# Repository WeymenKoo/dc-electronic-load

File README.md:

# DC Electronic Load

A 150 W programmable DC load (0.6 to 58 V, 0 to 10.1 A) for testing power supplies, batteries and precision current sources.
Built to be better than the AliExpress DL24-class loads and far cheaper than a bench load: four TO-247 MOSFETs each with its own
current loop, hardware CC and CV, real protection, 16-bit readback, galvanic isolation from the PC, and a local OLED + encoder panel so
no computer is needed for simple tests. One USB-C port powers it and carries SCPI (CDC) and DFU.

**Current revision: Rev E** (schematic complete and verified; 2-layer PCB panel created with every part placed, routing not started).
Rev E is the Rev D architecture built as cheaply as JLCPCB / LCSC allow: about US$25 of catalogue parts per unit plus the OLED module,
blower and PCB (`docs/rev_e_specification.md`, section 14). Rev D (Nov 2026) was the same architecture with LT1014 / LT1013 op-amps, a
MAX7219 7-segment panel, a 12 V boost for the fan and a 4-layer panel; Rev B was built in Nov 2024 as two Altium boards; Rev C was a
redesign of the power board around the Rev B control board.

## Folder map

| Folder | What is in it |
|---|---|
| `hardware/` | **Rev E KiCad 10 project**, project libraries, the generator, netlist checker, placer and JLCPCB pricing tools, outputs (PDF schematic, ERC, BOM with LCSC codes and prices, placed-board drawing). See `hardware/README.md` |
| `simulation/` | LTspice decks 00 to 06 for the Rev C analog stage (LT1014 / LT1013, reference results kept) and `rev_e/` with decks 01 to 04 and 06 re-run on the TLV9154. README with both results tables |
| `docs/` | `rev_e_specification.md` (ratings, architecture, isolation, thresholds, layout rules, bring-up, open items, cost), `firmware_requirements.md`, `design_review_rev_b.md` (why Rev B was replaced), MOSFET selection, heatsink plan, comparison with the cheap loads, Rev B design notes spreadsheet |
| `datasheets/` | component datasheets and app notes (`appnotes/`) |
| `reference/` | other people's DC load designs used as references (Scullcom, Jay Diddy B, Kerry Wong) and heatsink / cooler CAD |
| `archive/` | the built Altium revisions: Rev A (May 2024), Rev A2 "cheaper" (Jul 2024), Rev B control, power and UI boards (Nov 2024) with gerbers, the Rev B bring-up firmware, the Rev B netlists used for the review, early LTspice experiments |

## Start here
1. `docs/rev_e_specification.md`: what the instrument is, what Rev E changed to get the cost down, and why every block exists.
2. `hardware/outputs/rev_e_v1/DC_Load_RevE_schematic.pdf`: 14 pages, page 1 is the block diagram. `BOM_RevE_JLC.csv` is the priced BOM.
3. `simulation/README.md`, then open `simulation/rev_e/01_dc_transfer/01_dc_transfer.asc` in LTspice.
4. `docs/design_review_rev_b.md` if you want to know what went wrong before.

## Status and next steps
- [x] Rev B review, Rev C analog redesign simulated (decks 01 to 06)
- [x] Rev D schematic (control + power board, isolated, USB-C): ERC clean, netlist proven against the simulation
- [x] Rev E cost reduction: TLV9154 re-simulation (decks 01 to 04, 06), schematic regenerated, every part sourced at JLCPCB / LCSC, 2-layer 170 × 100 mm panel placed
- [ ] Order: PCB (2-layer, 2 oz, 170 × 100 mm panel), the LCSC parts from `BOM_RevE_JLC.csv`, the off-board items (spec section 14). Verify the items in spec section 13 first (DC-DC pin order, OLED pin order, nBOOT_SEL)
- [ ] PCB routing by hand (rules in the spec, section 11), then the bring-up plan
- [ ] Firmware (`docs/firmware_requirements.md`)
- [ ] Measure the heatsink Rsa with the blower duct fitted and set the firmware power limits (fanless is about 25 W)

## Tools
KiCad 10 (schematic generated by `hardware/tools/build_reve.py`, Python 3, no dependencies), LTspice 24+ (run from a local copy, see
`simulation/README.md`), kicad-cli for the exports, the JLCPCB parts API for prices (`hardware/tools/jlc_price.py`).

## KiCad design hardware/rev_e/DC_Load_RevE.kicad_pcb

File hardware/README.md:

# Hardware: Rev E KiCad project

```
hardware/
├── rev_e/                 KiCad 10 project: DC_Load_RevE.kicad_pro, root sheet + sheets/ (14 pages), DC_Load_RevE.kicad_pcb (placed, not routed)
├── libraries/             project symbols (dcload.kicad_sym) and footprints (dcload.pretty), registered as ${KIPRJMOD}/../libraries
├── tools/                 build_reve.py generates every sheet; check_netlist_reve.py verifies the result; place_reve.py builds the placed PCB;
│                          jlc_price.py / jlc_bom_price.py price parts at JLCPCB (LCSC); kgen.py / sexp.py are the writer
└── outputs/rev_e_v1/      DC_Load_RevE_schematic.pdf, ERC_report.txt (0 / 0), DC_Load_RevE.xml netlist, BOM_RevE.csv (with LCSC codes),
                           BOM_RevE_JLC.csv (priced), DC_Load_RevE_placement.pdf, placement_top.png
```

## Status
Rev E is the cost-reduced build of the Rev D architecture (what changed and why: `../docs/rev_e_specification.md`, section 1).
Schematic complete, ERC 0 errors / 0 warnings, lint 0, netlist verified against the Rev E LTspice deck 06 (`../simulation/rev_e`).
**PCB: every footprint placed on a 2-layer 170 × 100 mm panel, no tracks or zones yet.** `place_reve.py` builds the panel (control board 170 × 40
on top, V-score at y 40, power board 170 × 60 = the heatsink base), the L-shaped 4 mm isolation keep-out on both copper layers, the heatsink and
FET drawing, mounting and screw-access holes, places all 211 footprints (J10 on the back of the control board, the TO-247 hand-soldered under the
power board, everything else on F.Cu) and puts every reference label in a free spot. DRC on the placed board: no violations (the 4
`lib_footprint_issues` are KiCad library-revision notes). Routing is the next step, by hand in KiCad, rules in the spec section 11.

## Regenerating
```
cd hardware/tools
python3 build_reve.py                      # rewrites ../rev_e/*.kicad_sch and the dcload symbol library (hand edits in KiCad are lost); exits 1 on any lint violation
KC=/Applications/KiCad/KiCad.app/Contents/MacOS/kicad-cli
cd ../rev_e
$KC sch erc --format report --severity-all -o ../outputs/rev_e_v1/ERC_report.txt DC_Load_RevE.kicad_sch
$KC sch export netlist --format kicadxml -o ../outputs/rev_e_v1/DC_Load_RevE.xml DC_Load_RevE.kicad_sch
python3 ../tools/check_netlist_reve.py ../outputs/rev_e_v1/DC_Load_RevE.xml ../../simulation/rev_e/06_cv_mode/06_cv_mode.net
$KC sch export pdf -o ../outputs/rev_e_v1/DC_Load_RevE_schematic.pdf DC_Load_RevE.kicad_sch
$KC sch export bom --fields 'Reference,Value,Footprint,MPN,LCSC,Tolerance,${QUANTITY}' --labels 'Refs,Value,Footprint,MPN,LCSC,Tolerance,Qty' \
    --group-by 'Value,Footprint,MPN,LCSC,Tolerance' --ref-range-delimiter '' --exclude-dnp -o ../outputs/rev_e_v1/BOM_RevE.csv DC_Load_RevE.kicad_sch
python3 ../tools/jlc_bom_price.py ../outputs/rev_e_v1/BOM_RevE.csv 1       # -> BOM_RevE_JLC.csv, live JLCPCB prices (argument = number of boards)
# placed PCB from the netlist (KiCad's own python has pcbnew):
/Applications/KiCad/KiCad.app/Contents/Frameworks/Python.framework/Versions/Current/bin/python3 ../tools/place_reve.py
$KC pcb drc --format json --severity-all -o /tmp/drc.json DC_Load_RevE.kicad_pcb
```
Once you start editing in KiCad, stop running the generator and the placer (or port your edits into them): both overwrite their output files.

## Sourcing
Every bought part carries an `LCSC` field in the schematic, so the BOM export and JLCPCB's assembly upload line up. `jlc_price.py KEYWORD` looks a
part up (code, stock, basic/extended, price ladder); `jlc_bom_price.py` prices the whole BOM, searching JLC basic parts for the generic 0603 / 0805 /
1206 resistors and capacitors that have no code. Off-board items (OLED module, 5 V blower, NTC lug, ribbon cable, M4 hardware) are listed in the
spec, section 14.

## Drawing rules (enforced by `kgen.Sch.lint`; the build fails on any violation)
- A3 landscape for every sheet. JetBrains Mono everywhere: 4.5 mm sheet title, 2.5 mm block titles, 2.0 mm notes (dark grey), 1.6 mm references and values, 1.4 mm labels. 1.27 mm grid.
- Every circuit sits in a titled block frame fitted to its content with a 6 mm margin; the whole drawing is centred in the drawable area (18 mm from the paper edge, title-block corner kept clear).
- No text overlaps any text, symbol or wire; no symbol overlaps another or a foreign wire; block frames never overlap.
- At most 3 wires per junction (staggered joints instead of 4-way crosses). Wire crossings are drawn with hop-overs (`hop_over_display` in the project file) and kept rare.
- The power sheet is drawn as a tree (trunk, branches, one rail symbol per branch end). The isolation barrier is a red dashed line on every sheet it crosses.
- The root sheet is a wired block diagram: sheet pins on all four sides of a block (`kgen.add_sheet` sides L / R / T / B), straight wires between pins at the same row, one hop-over (DRAIN over KILL). Nets that reach three or more blocks use a second, pass-through pin name on the sub-sheet (`VSET_MON`, `VSEN_OA_OVP`, `KILL_T` / `VSET_T` / `AVG_T` / `DRAIN_T`); KiCad's `multiple_net_names` warning is set to *ignore* in the project file for that reason, and `check_netlist_reve.py` folds those names back onto their nets.
- Nets are colour-coded (key on the root sheet): DUT current path (0.6 mm, brown), set-point (magenta), measurement (blue), protection (orange), isolated SPI (violet), USB data (teal), supply rails (red).

## Sheets
| Page | Sheet | Content |
|---|---|---|
| 1 | Root | **Block diagram**: every sub-sheet is a block and every connection a wire between sheet pins (no net labels); signal flow left to right, the four channels daisy-chained through `*_T` pass-through pins, barrier, colour key |
| 2 | USB & Power | USB-C, CC sense, ESD; power tree: AP2112K 3.3 V, isolated DC-DC + 78L05; blower switch (5 V); star point |
| 3 | MCU | STM32G0B1RBT6, decoupling, reset / BOOT / SWD, UART, heartbeat LED |
| 4 | Front Panel UI | OLED header + I2C pull-ups, encoder, 3 buttons, ON / FAULT LEDs |
| 5 | Board Link | J10 (control board, back face) to J11 (power board) over the 12-way IDC ribbon; `_LK` nets; CBL1 BOM line |
| 6 | Isolated Interface | CA-IS3761HW isolator, MCP4822 DAC, ADS1118 ADC |
| 7 | Setpoint & CV | V_SET divider, OTP / OFF pull-downs, hardware CV error amp (U12C) |
| 8 | Sense | ISEN averaging amp (U12A), VSEN 4-wire difference amp (U12B), ADC clamps |
| 9 | Protection | NTC, LM339 OTP / dropout-KILL / NTC-open / OVP, OFF diode-OR, analog supplies |
| 10 | Power Path | M4 terminals, soldered 58 V mini-blade fuse, TVS, snubber, 4-wire sense with fallback |
| 11-14 | Channel 1-4 | One TLV9154 section, 3.3k / 1n / 47R, IRFP250N, 2 × 0.2R Kelvin sense, KILL, 15M offset |

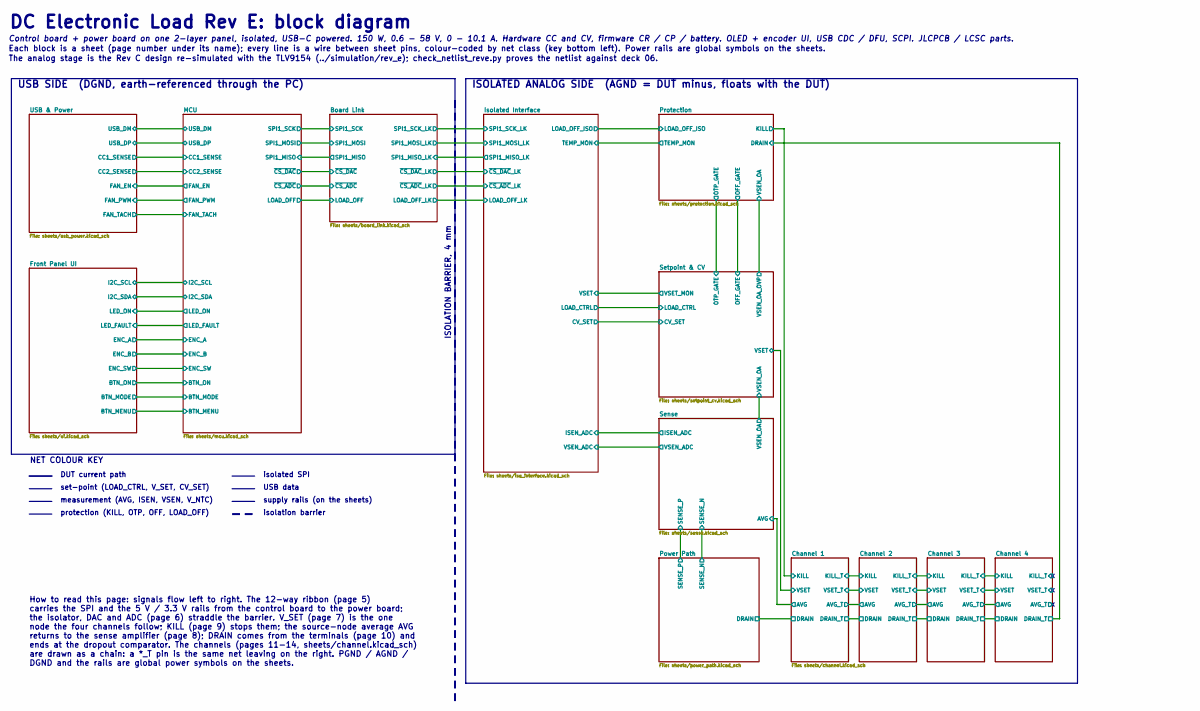
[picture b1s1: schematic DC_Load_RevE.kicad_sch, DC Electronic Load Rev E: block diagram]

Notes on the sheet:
DC Electronic Load Rev E: block diagram
Control board + power board on one 2-layer panel, isolated, USB-C powered. 150 W, 0.6 - 58 V, 0 - 10.1 A. Hardware CC and CV, firmware CR / CP / battery. OLED + encoder UI, USB CDC / DFU, SCPI. JLCPCB / LCSC parts.
Each block is a sheet (page number under its name); every line is a wire between sheet pins, colour-coded by net class (key bottom left). Power rails are global symbols on the sheets.
The analog stage is the Rev C design re-simulated with the TLV9154 (../simulation/rev_e); check_netlist_reve.py proves the netlist against deck 06.
USB SIDE (DGND, earth-referenced through the PC)
ISOLATED ANALOG SIDE (AGND = DUT minus, floats with the DUT)
ISOLATION BARRIER, 4 mm
NET COLOUR KEY
DUT current path
set-point (LOAD_CTRL, V_SET, CV_SET)
measurement (AVG, ISEN, VSEN, V_NTC)
protection (KILL, OTP, OFF, LOAD_OFF)
isolated SPI
USB data
supply rails (on the sheets)
isolation barrier
How to read this page: signals flow left to right. The 12-way ribbon (page 5) carries the SPI and the 5 V / 3.3 V rails from the control board to the power board; the isolator, DAC and ADC (page 6) straddle the barrier. V_SET (page 7) is the one node the four channels follow; KILL (page 9) stops th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

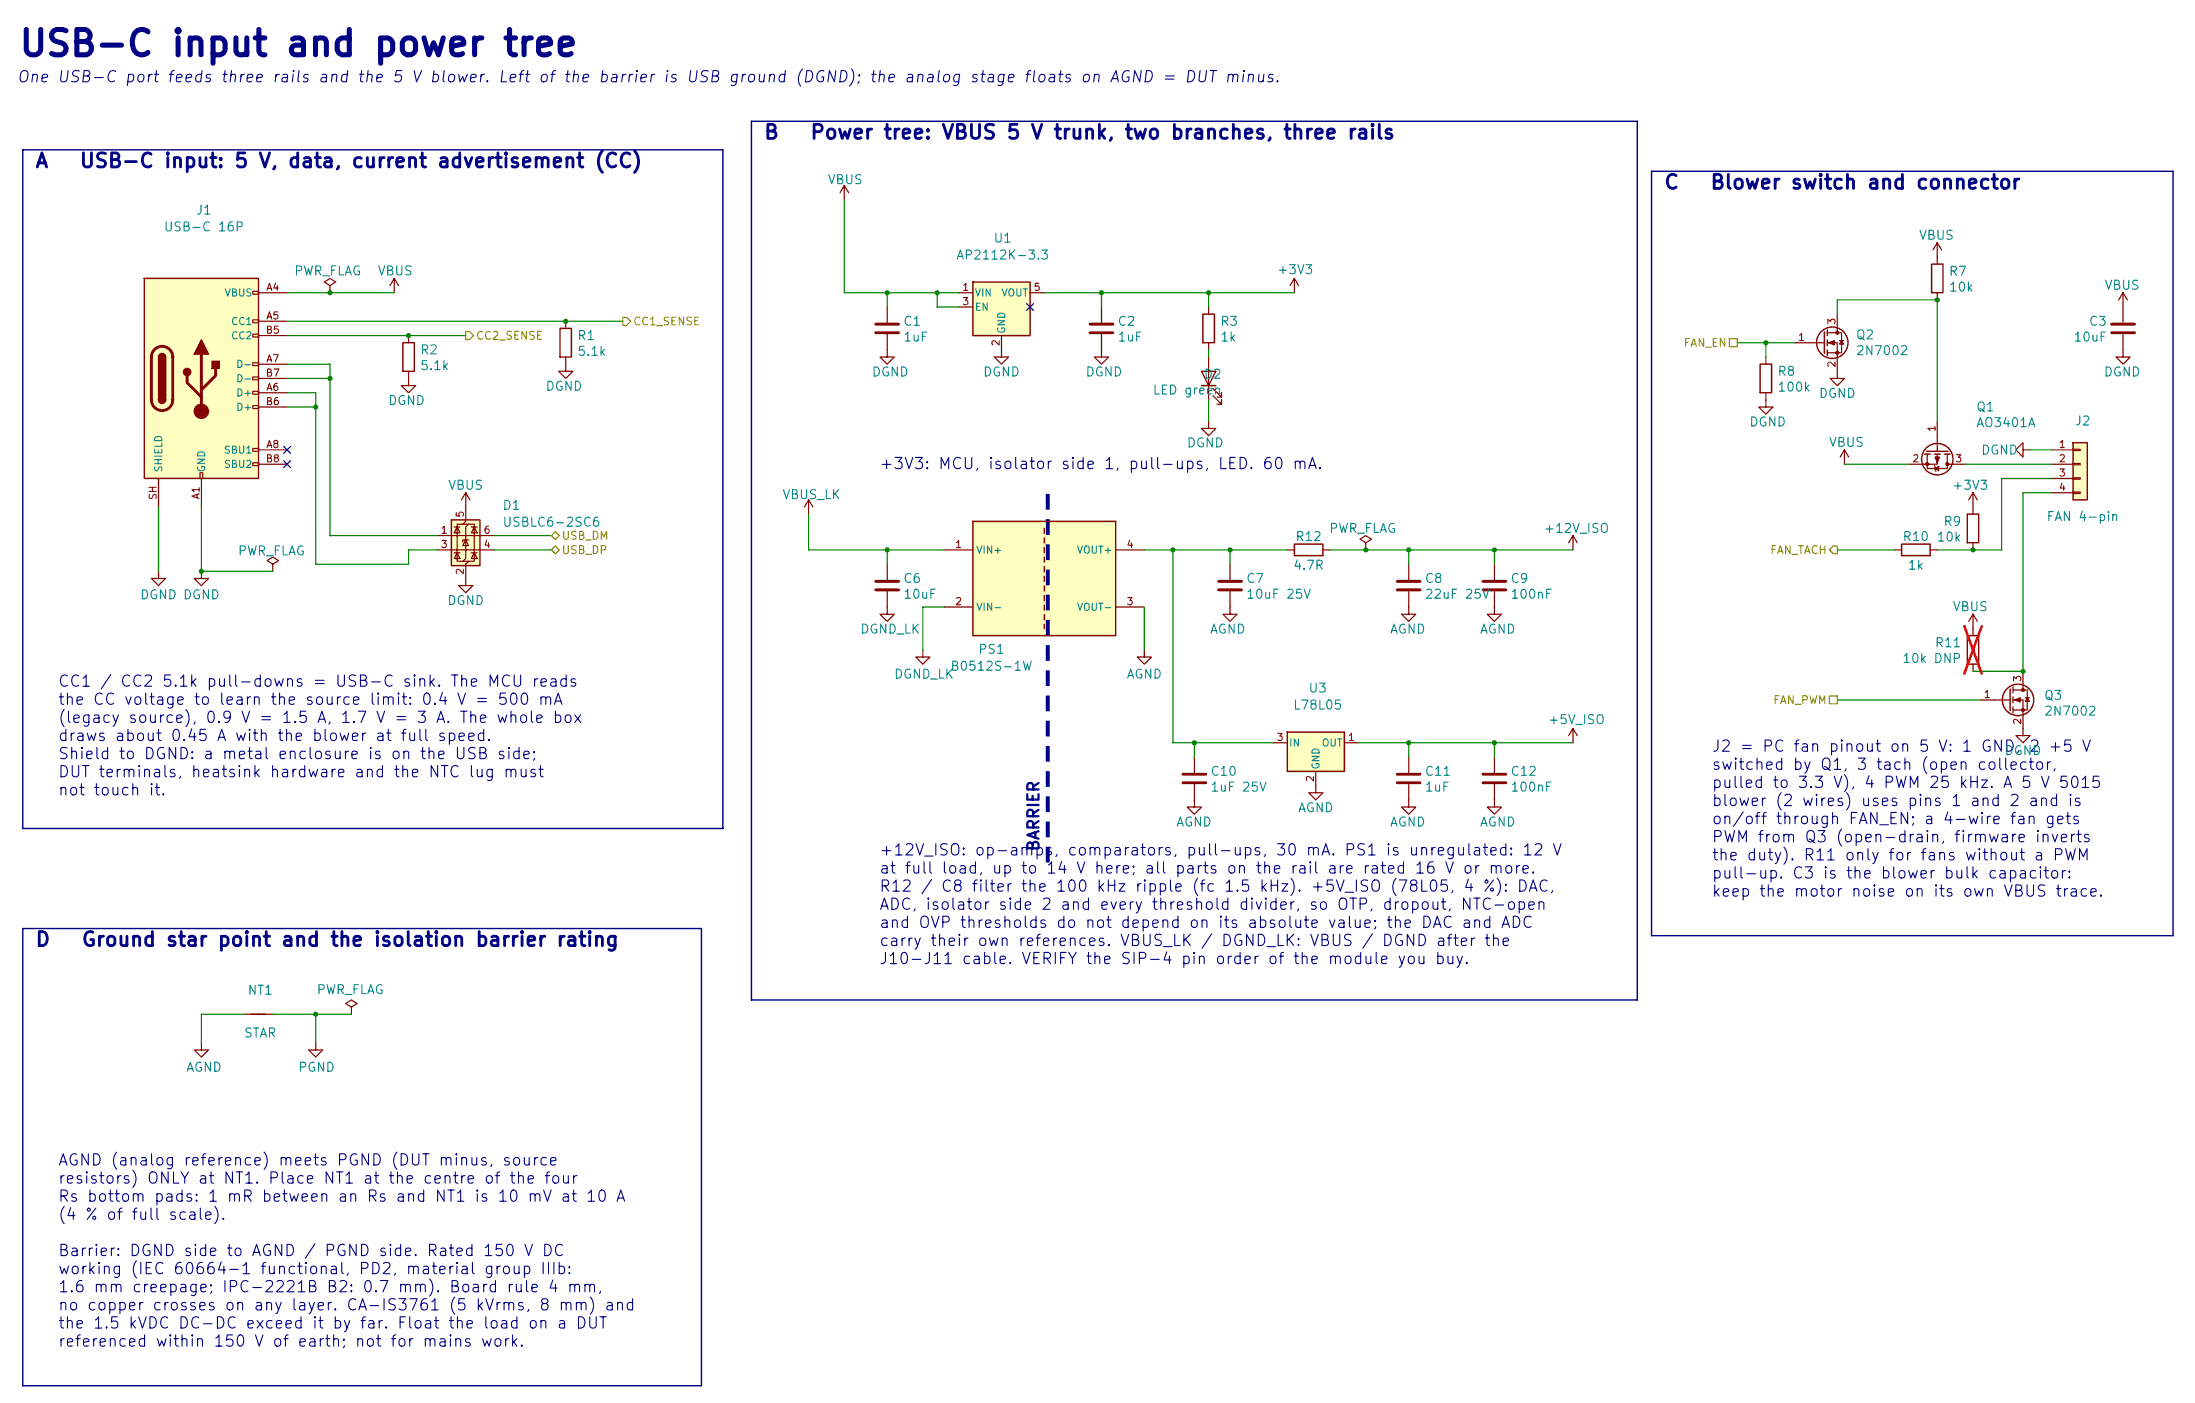
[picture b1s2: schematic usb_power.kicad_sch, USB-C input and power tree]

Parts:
C1, C2, C11: 1uF; C_0603_1608Metric
C3, C6: 10uF; C_0805_2012Metric
C7: 10uF 25V; C_0805_2012Metric
C8: 22uF 25V; C_1206_3216Metric
C9, C12: 100nF; C_0603_1608Metric
C10: 1uF 25V; C_0603_1608Metric
D1: USBLC6-2SC6; SOT-23-6; LCSC C5261088
D2: LED green; LED_0603_1608Metric; MPN KT-0603G; LCSC C12624
J1: USB-C 16P; USB_C_Receptacle_HRO_TYPE-C-31-M-12; MPN HRO TYPE-C-31-M-12 (16 pin, USB 2.0); LCSC C165948
J2: FAN 4-pin; JST_XH_B4B-XH-A_1x04_P2.50mm_Vertical; MPN JST B4B-XH-A(LF)(SN); LCSC C144395
NT1: STAR; NetTie-2_SMD_Pad2.0mm
PS1: B0512S-1W; SIP-4_P2.54mm_DCDC_1W; MPN DEXU B0512S-1W (LCSC C5244116, 1.5 kV);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; LCSC C5244116
Q1: AO3401A; SOT-23; LCSC C15127
Q2, Q3: 2N7002; SOT-23; LCSC C8545
R1, R2: 5.1k; R_0603_1608Metric; Tolerance 1%
R3, R10: 1k; R_0603_1608Metric
R7, R9: 10k; R_0603_1608Metric
R8: 100k; R_0603_1608Metric
R11: 10k DNP; R_0603_1608Metric; not fitted
R12: 4.7R; R_1206_3216Metric
U1: AP2112K-3.3; SOT-23-5; LCSC C23380830
U3: L78L05; SOT-89-3; MPN L78L05ABUTR (SOT-89); LCSC C42738

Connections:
+3V3: C2.1, R3.1, R9.1, U1.5 (VOUT); also elsewhere on the board
+5V_ISO: C11.1, C12.1, U3.1 (OUT); also elsewhere on the board
+12V_ISO: C8.1, C9.1, R12.2; also elsewhere on the board
/MCU/CC1_SENSE: J1.A5 (CC1), R1.1; also elsewhere on the board
/MCU/CC2_SENSE: J1.B5 (CC2), R2.1; also elsewhere on the board
/MCU/FAN_EN: Q2.1 (G), R8.1; also elsewhere on the board
/MCU/FAN_PWM: Q3.1 (G); also elsewhere on the board
/MCU/FAN_TACH: R10.1; also elsewhere on the board
/MCU/USB_DM: D1.6 (I/O1); also elsewhere on the board
/MCU/USB_DP: D1.4 (I/O2); also elsewhere on the board
AGND: C7.2, C8.2, C9.2, C10.2, C11.2, C12.2, NT1.1, PS1.3 (VOUT-), U3.2 (GND); also elsewhere on the board
DGND: C1.2, C2.2, C3.2, D1.2 (GND), D2.1 (K), J1.A1 (GND), J1.A12 (GND), J1.B1 (GND), J1.B12 (GND), J1.SH (SHIELD), J2.1, Q2.2 (S), Q3.2 (S), R1.2, R2.2, R8.2, U1.2 (GND); also elsewhere on the board
DGND_LK: C6.2, PS1.2 (VIN-); also elsewhere on the board
unnamed: D1.1 (I/O1), J1.A7 (D-), J1.B7 (D-)
unnamed: D1.3 (I/O2), J1.A6 (D+), J1.B6 (D+)
unnamed: D2.2 (A), R3.2
unnamed: J2.2, Q1.3 (D)
unnamed: J2.3, R9.2, R10.2
unnamed: J2.4, Q3.3 (D), R11.2
unnamed: C7.1, C10.1, PS1.4 (VOUT+), R12.1, U3.3 (IN)
unnamed: Q1.1 (G), Q2.3 (D), R7.2
PGND: NT1.2; also elsewhere on the board
VBUS: C1.1, C3.1, D1.5 (VBUS), J1.A4 (VBUS), J1.A9 (VBUS), J1.B4 (VBUS), J1.B9 (VBUS), Q1.2 (S), R7.1, R11.1, U1.1 (VIN), U1.3 (EN); also elsewhere on the board
VBUS_LK: C6.1, PS1.1 (VIN+); also elsewhere on the board

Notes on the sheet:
USB-C input and power tree
One USB-C port feeds three rails and the 5 V blower. Left of the barrier is USB ground (DGND); the analog stage floats on AGND = DUT minus.
CC1 / CC2 5.1k pull-downs = USB-C sink. The MCU reads the CC voltage to learn the source limit: 0.4 V = 500 mA (legacy source), 0.9 V = 1.5 A, 1.7 V = 3 A. The whole box draws about 0.45 A with the blower at full speed. Shield to DGND: a metal enclosure is on the USB side; DUT terminals, heatsink h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
A USB-C input: 5 V, data, current advertisement (CC)
AGND (analog reference) meets PGND (DUT minus, source resistors) ONLY at NT1. Place NT1 at the centre of the four Rs bottom pads: 1 mR between an Rs and NT1 is 10 mV at 10 A (4 % of full scale). Barrier: DGND side to AGND / PGND side. Rated 150 V DC working (IEC 60664-1 functional, PD2, material gr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
D Ground star point and the isolation barrier rating
+3V3: MCU, isolator side 1, pull-ups, LED. 60 mA.
BARRIER
+12V_ISO: op-amps, comparators, pull-ups, 30 mA. PS1 is unregulated: 12 V at full load, up to 14 V here; all parts on the rail are rated 16 V or more. R12 / C8 filter the 100 kHz ripple (fc 1.5 kHz). +5V_ISO (78L05, 4 %): DAC, ADC, isolator side 2 and every threshold divider, so OTP, dropout, NTC-o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
B Power tree: VBUS 5 V trunk, two branches, three rails
J2 = PC fan pinout on 5 V: 1 GND, 2 +5 V switched by Q1, 3 tach (open collector, pulled to 3.3 V), 4 PWM 25 kHz. A 5 V 5015 blower (2 wires) uses pins 1 and 2 and is on/off through FAN_EN; a 4-wire fan gets PWM from Q3 (open-drain, firmware inverts the duty). R11 only for fans without a PWM pull-up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
C Blower switch and connector

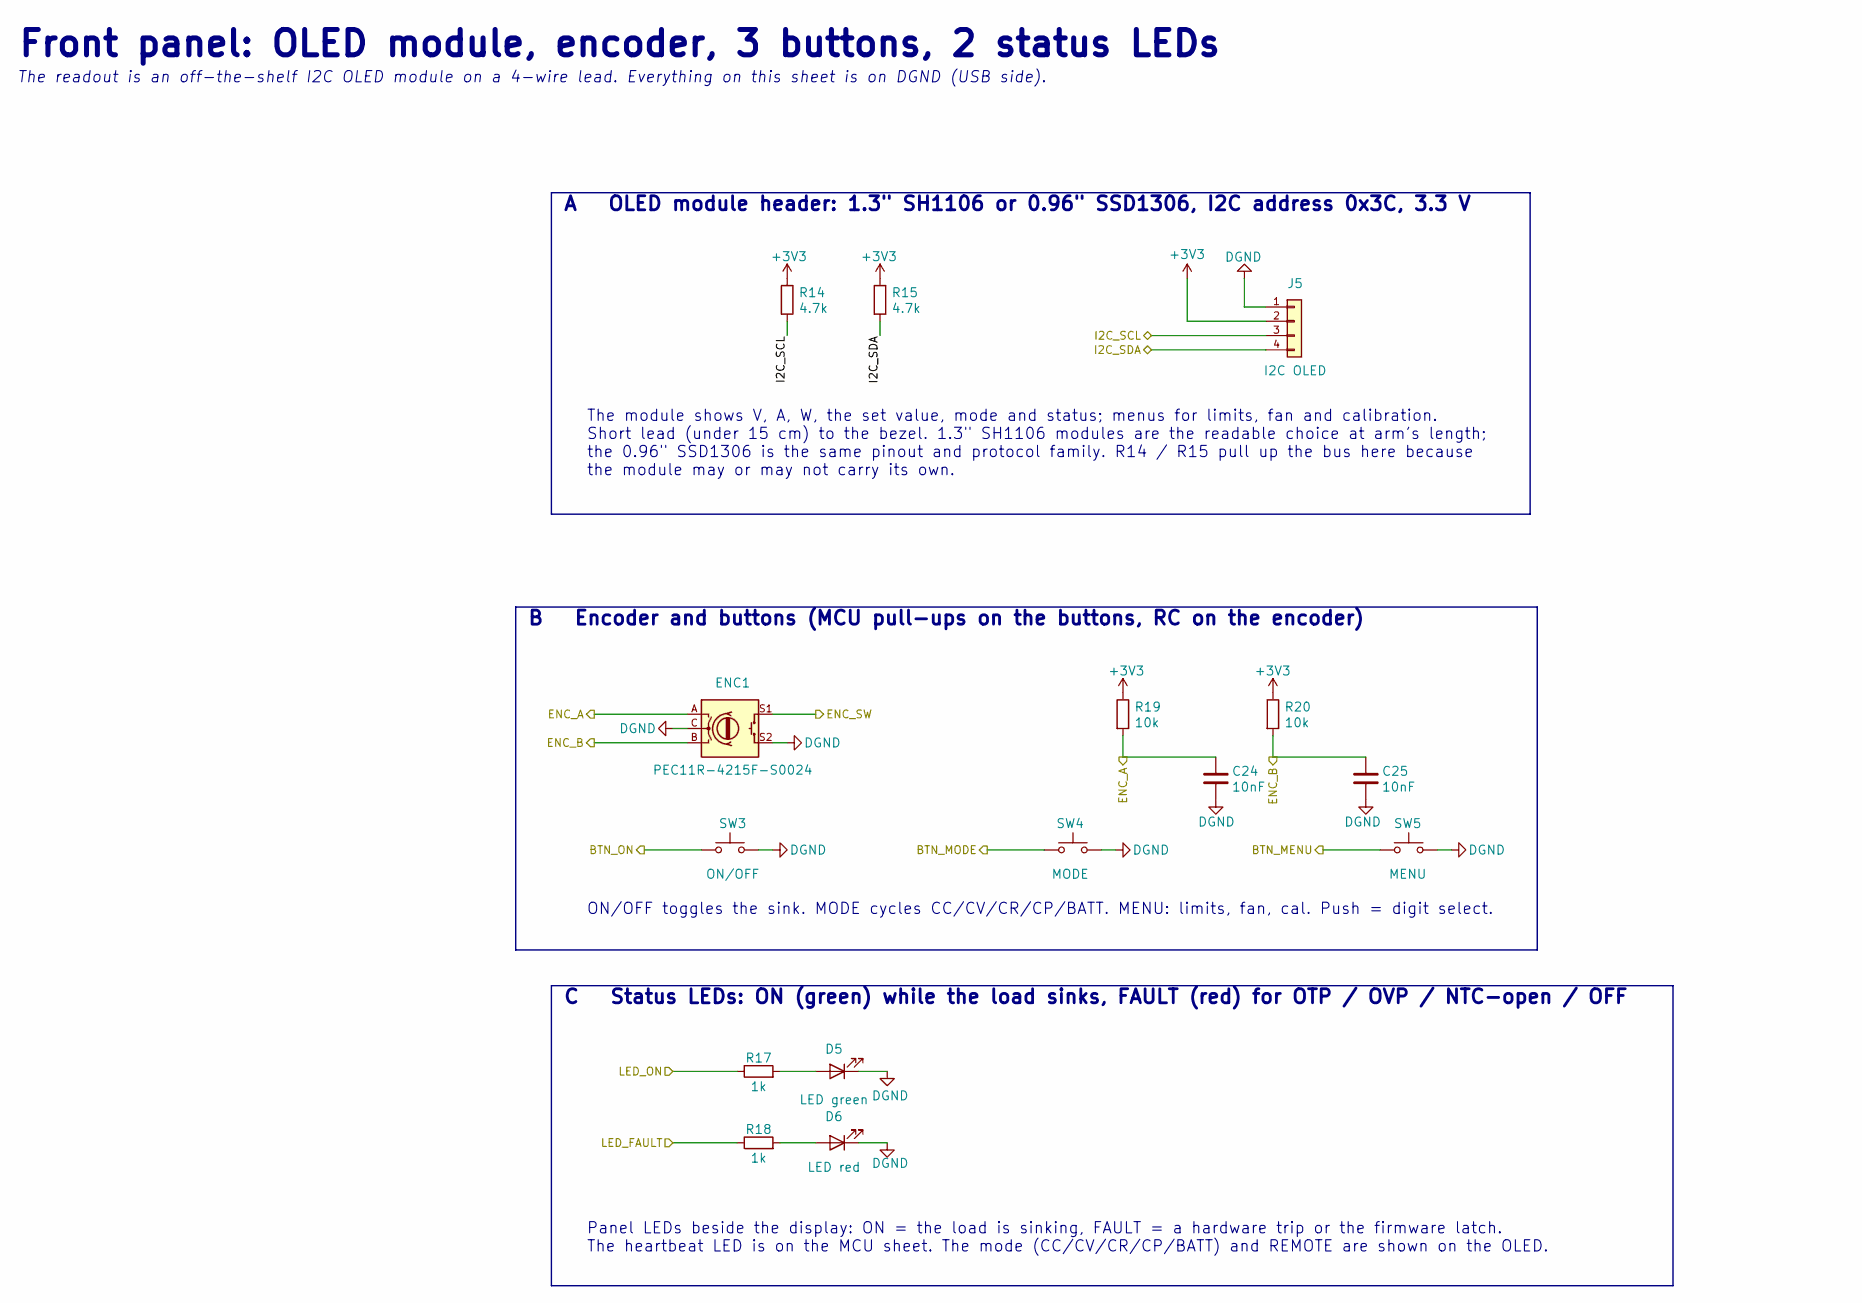
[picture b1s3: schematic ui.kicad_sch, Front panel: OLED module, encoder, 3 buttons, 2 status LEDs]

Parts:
C24, C25: 10nF; C_0603_1608Metric
D5: LED green; LED_0603_1608Metric; MPN KT-0603N; LCSC C12624
D6: LED red; LED_0603_1608Metric; MPN KT-0603D; LCSC C2286
ENC1: PEC11R-4215F-S0024; RotaryEncoder_Alps_EC11E-Switch_Vertical_H20mm; MPN Bourns PEC11R-4215F-S0024 (24 detents, 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; LCSC C143790
J5: I2C OLED; PinHeader_1x04_P2.54mm_Vertical; MPN B-2100S04P-A110 (the OLED module itself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; LCSC C124378
R14, R15: 4.7k; R_0603_1608Metric
R17, R18: 1k; R_0603_1608Metric
R19, R20: 10k; R_0603_1608Metric
SW3: ON/OFF; SW_PUSH_6mm; MPN KH-6X6X5H-TJ 6 x 6 mm tact switch; LCSC C2837515
SW4: MODE; SW_PUSH_6mm; MPN KH-6X6X5H-TJ 6 x 6 mm tact switch; LCSC C2837515
SW5: MENU; SW_PUSH_6mm; MPN KH-6X6X5H-TJ 6 x 6 mm tact switch; LCSC C2837515

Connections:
+3V3: J5.2, R14.1, R15.1, R19.1, R20.1; also elsewhere on the board
/Front Panel UI/BTN_MENU: SW5.1; also elsewhere on the board
/Front Panel UI/BTN_MODE: SW4.1; also elsewhere on the board
/Front Panel UI/BTN_ON: SW3.1; also elsewhere on the board
/Front Panel UI/ENC_A: C24.1, ENC1.A, R19.2; also elsewhere on the board
/Front Panel UI/ENC_B: C25.1, ENC1.B, R20.2; also elsewhere on the board
/Front Panel UI/ENC_SW: ENC1.S1; also elsewhere on the board
/Front Panel UI/I2C_SCL: J5.3, R14.2; also elsewhere on the board
/Front Panel UI/I2C_SDA: J5.4, R15.2; also elsewhere on the board
/Front Panel UI/LED_FAULT: R18.1; also elsewhere on the board
/Front Panel UI/LED_ON: R17.1; also elsewhere on the board
DGND: C24.2, C25.2, D5.1 (K), D6.1 (K), ENC1.C, ENC1.S2, J5.1, SW3.2, SW4.2, SW5.2; also elsewhere on the board
unnamed: D5.2 (A), R17.2
unnamed: D6.2 (A), R18.2

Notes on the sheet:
Front panel: OLED module, encoder, 3 buttons, 2 status LEDs
The readout is an off-the-shelf I2C OLED module on a 4-wire lead. Everything on this sheet is on DGND (USB side).
The module shows V, A, W, the set value, mode and status; menus for limits, fan and calibration. Short lead (under 15 cm) to the bezel. 1.3" SH1106 modules are the readable choice at arm's length; the 0.96" SSD1306 is the same pinout and protocol family. R14 / R15 pull up the bus here because the m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
A OLED module header: 1.3" SH1106 or 0.96" SSD1306, I2C address 0x3C, 3.3 V
ON/OFF toggles the sink. MODE cycles CC/CV/CR/CP/BATT. MENU: limits, fan, cal. Push = digit select.
B Encoder and buttons (MCU pull-ups on the buttons, RC on the encoder)
Panel LEDs beside the display: ON = the load is sinking, FAULT = a hardware trip or the firmware latch. The heartbeat LED is on the MCU sheet. The mode (CC/CV/CR/CP/BATT) and REMOTE are shown on the OLED.
C Status LEDs: ON (green) while the load sinks, FAULT (red) for OTP / OVP / NTC-open / OFF

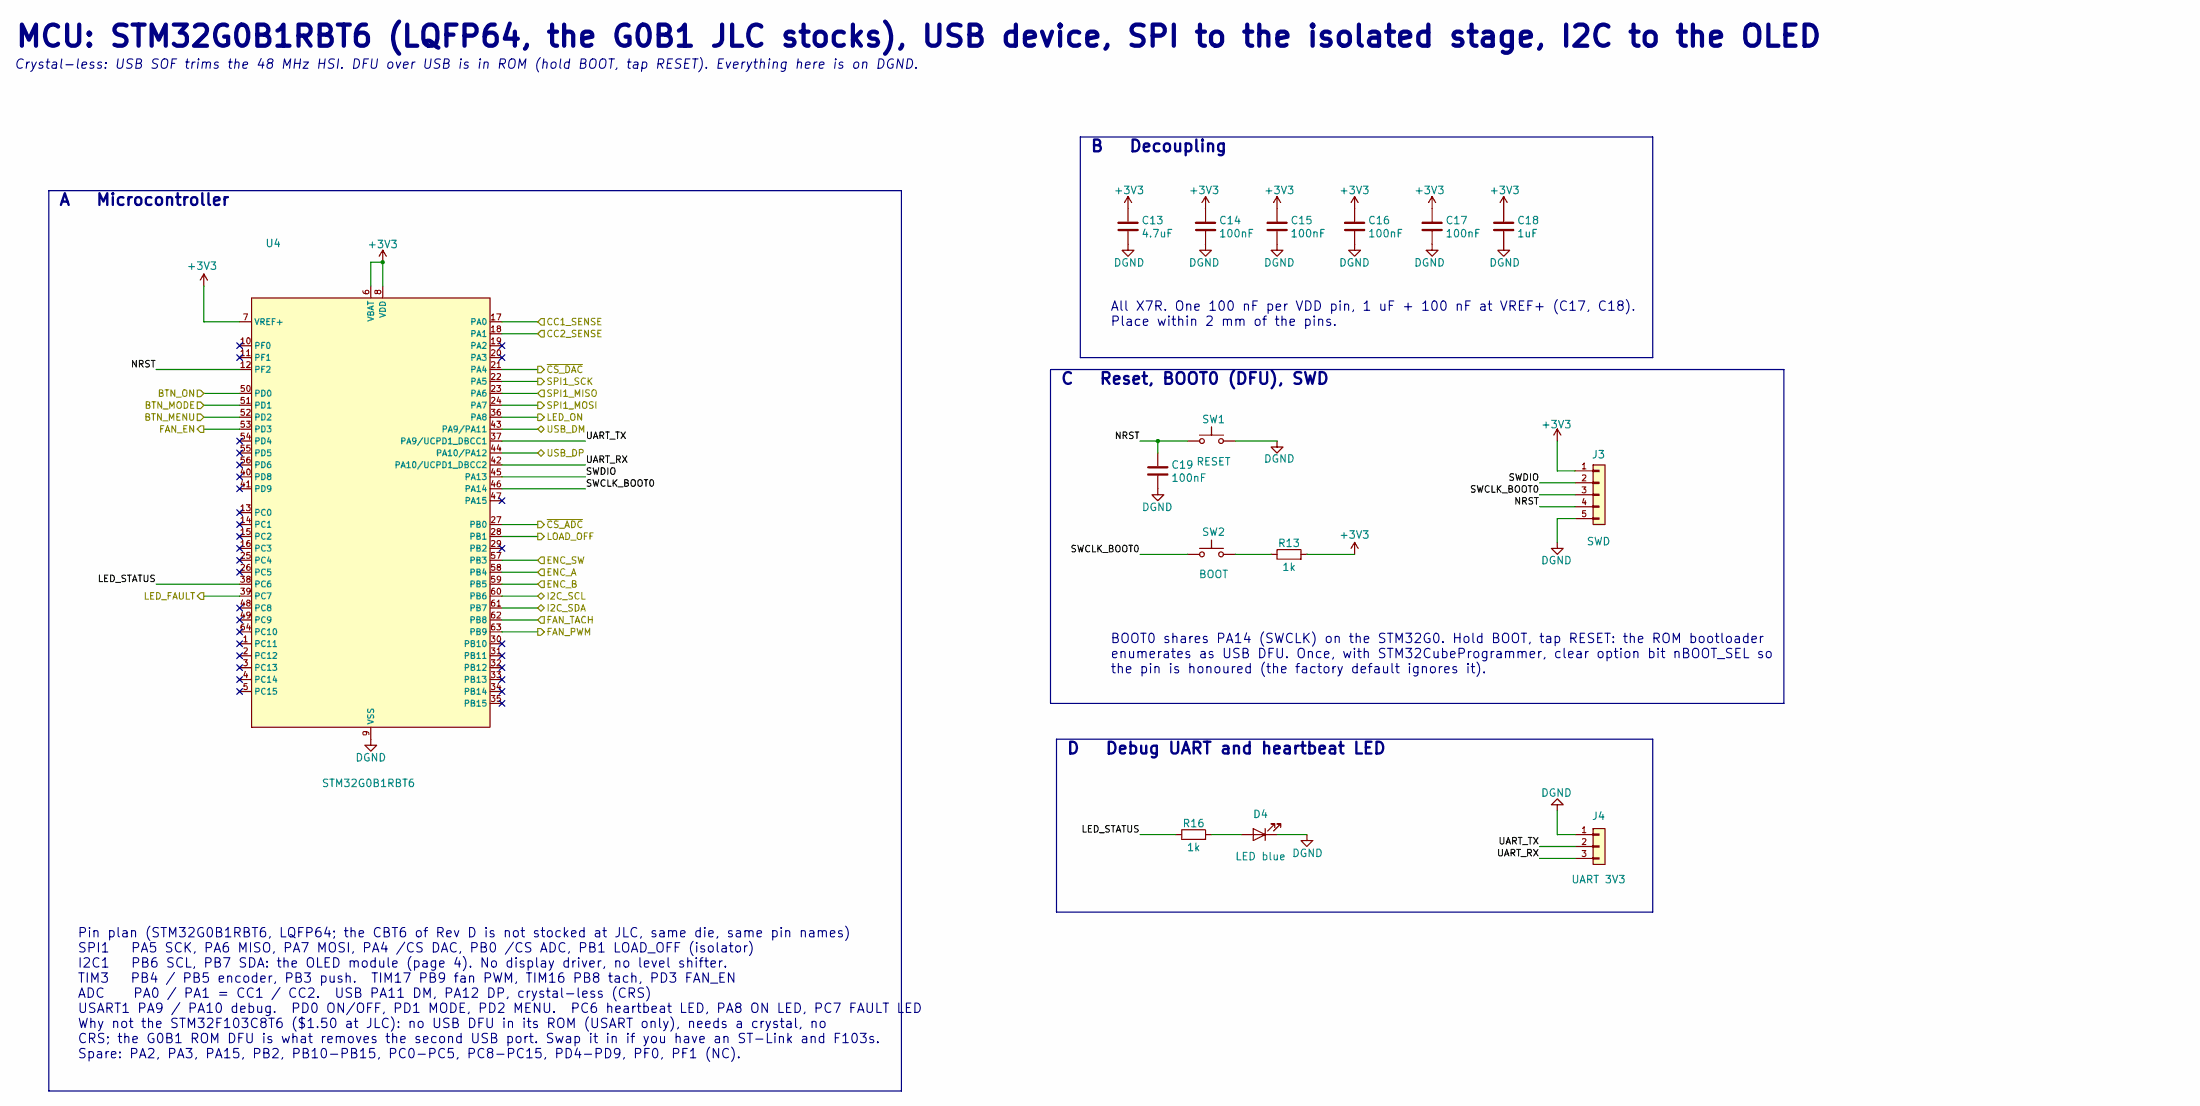
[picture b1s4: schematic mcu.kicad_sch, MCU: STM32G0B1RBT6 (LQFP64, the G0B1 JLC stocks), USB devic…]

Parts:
C13: 4.7uF; C_0805_2012Metric
C14, C15, C16, C17, C19: 100nF; C_0603_1608Metric
C18: 1uF; C_0603_1608Metric
D4: LED blue; LED_0603_1608Metric; MPN KT-0603B; LCSC C2288
J3: SWD; PinHeader_1x05_P2.54mm_Vertical; MPN B-2100S05P-A110; LCSC C124379
J4: UART 3V3; PinHeader_1x03_P2.54mm_Vertical; MPN B-2100S03P-A110; LCSC C124376
R13, R16: 1k; R_0603_1608Metric
SW1: RESET; SW_PUSH_6mm; MPN KH-6X6X5H-TJ; LCSC C2837515
SW2: BOOT; SW_PUSH_6mm; MPN KH-6X6X5H-TJ; LCSC C2837515
U4: STM32G0B1RBT6; LQFP-64_10x10mm_P0.5mm; MPN STM32G0B1RBT6; LCSC C5143679

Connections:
+3V3: C13.1, C14.1, C15.1, C16.1, C17.1, C18.1, J3.1, R13.2, U4.6 (VBAT), U4.7 (VREF+), U4.8 (VDD); also elsewhere on the board
/Board Link/LOAD_OFF: U4.28 (PB1); also elsewhere on the board
/Board Link/SPI1_MISO: U4.23 (PA6); also elsewhere on the board
/Board Link/SPI1_MOSI: U4.24 (PA7); also elsewhere on the board
/Board Link/SPI1_SCK: U4.22 (PA5); also elsewhere on the board
/Board Link/~CS_ADC: U4.27 (PB0); also elsewhere on the board
/Board Link/~CS_DAC: U4.21 (PA4); also elsewhere on the board
/Front Panel UI/BTN_MENU: U4.52 (PD2); also elsewhere on the board
/Front Panel UI/BTN_MODE: U4.51 (PD1); also elsewhere on the board
/Front Panel UI/BTN_ON: U4.50 (PD0); also elsewhere on the board
/Front Panel UI/ENC_A: U4.58 (PB4); also elsewhere on the board
/Front Panel UI/ENC_B: U4.59 (PB5); also elsewhere on the board
/Front Panel UI/ENC_SW: U4.57 (PB3); also elsewhere on the board
/Front Panel UI/I2C_SCL: U4.60 (PB6); also elsewhere on the board
/Front Panel UI/I2C_SDA: U4.61 (PB7); also elsewhere on the board
/Front Panel UI/LED_FAULT: U4.39 (PC7); also elsewhere on the board
/Front Panel UI/LED_ON: U4.36 (PA8); also elsewhere on the board
/MCU/CC1_SENSE: U4.17 (PA0); also elsewhere on the board
/MCU/CC2_SENSE: U4.18 (PA1); also elsewhere on the board
/MCU/FAN_EN: U4.53 (PD3); also elsewhere on the board
/MCU/FAN_PWM: U4.63 (PB9); also elsewhere on the board
/MCU/FAN_TACH: U4.62 (PB8); also elsewhere on the board
/MCU/LED_STATUS: R16.1, U4.38 (PC6)
/MCU/NRST: C19.1, J3.4, SW1.1, U4.12 (PF2)
/MCU/SWCLK_BOOT0: J3.3, SW2.1, U4.46 (PA14)
/MCU/SWDIO: J3.2, U4.45 (PA13)
/MCU/UART_RX: J4.3, U4.42 (PA10/UCPD1_DBCC2)
/MCU/UART_TX: J4.2, U4.37 (PA9/UCPD1_DBCC1)
/MCU/USB_DM: U4.43 (PA9/PA11); also elsewhere on the board
/MCU/USB_DP: U4.44 (PA10/PA12); also elsewhere on the board
DGND: C13.2, C14.2, C15.2, C16.2, C17.2, C18.2, C19.2, D4.1 (K), J3.5, J4.1, SW1.2, U4.9 (VSS); also elsewhere on the board
unnamed: D4.2 (A), R16.2
unnamed: R13.1, SW2.2

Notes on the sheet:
MCU: STM32G0B1RBT6 (LQFP64, the G0B1 JLC stocks), USB device, SPI to the isolated stage, I2C to the OLED
Crystal-less: USB SOF trims the 48 MHz HSI. DFU over USB is in ROM (hold BOOT, tap RESET). Everything here is on DGND.
Pin plan (STM32G0B1RBT6, LQFP64; the CBT6 of Rev D is not stocked at JLC, same die, same pin names) SPI1 PA5 SCK, PA6 MISO, PA7 MOSI, PA4 /CS DAC, PB0 /CS ADC, PB1 LOAD_OFF (isolator) I2C1 PB6 SCL, PB7 SDA: the OLED module (page 4). No display driver, no level shifter. TIM3 PB4 / PB5 encoder, PB3 p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
A Microcontroller
All X7R. One 100 nF per VDD pin, 1 uF + 100 nF at VREF+ (C17, C18). Place within 2 mm of the pins.
B Decoupling
BOOT0 shares PA14 (SWCLK) on the STM32G0. Hold BOOT, tap RESET: the ROM bootloader enumerates as USB DFU. Once, with STM32CubeProgrammer, clear option bit nBOOT_SEL so the pin is honoured (the factory default ignores it).
C Reset, BOOT0 (DFU), SWD
D Debug UART and heartbeat LED

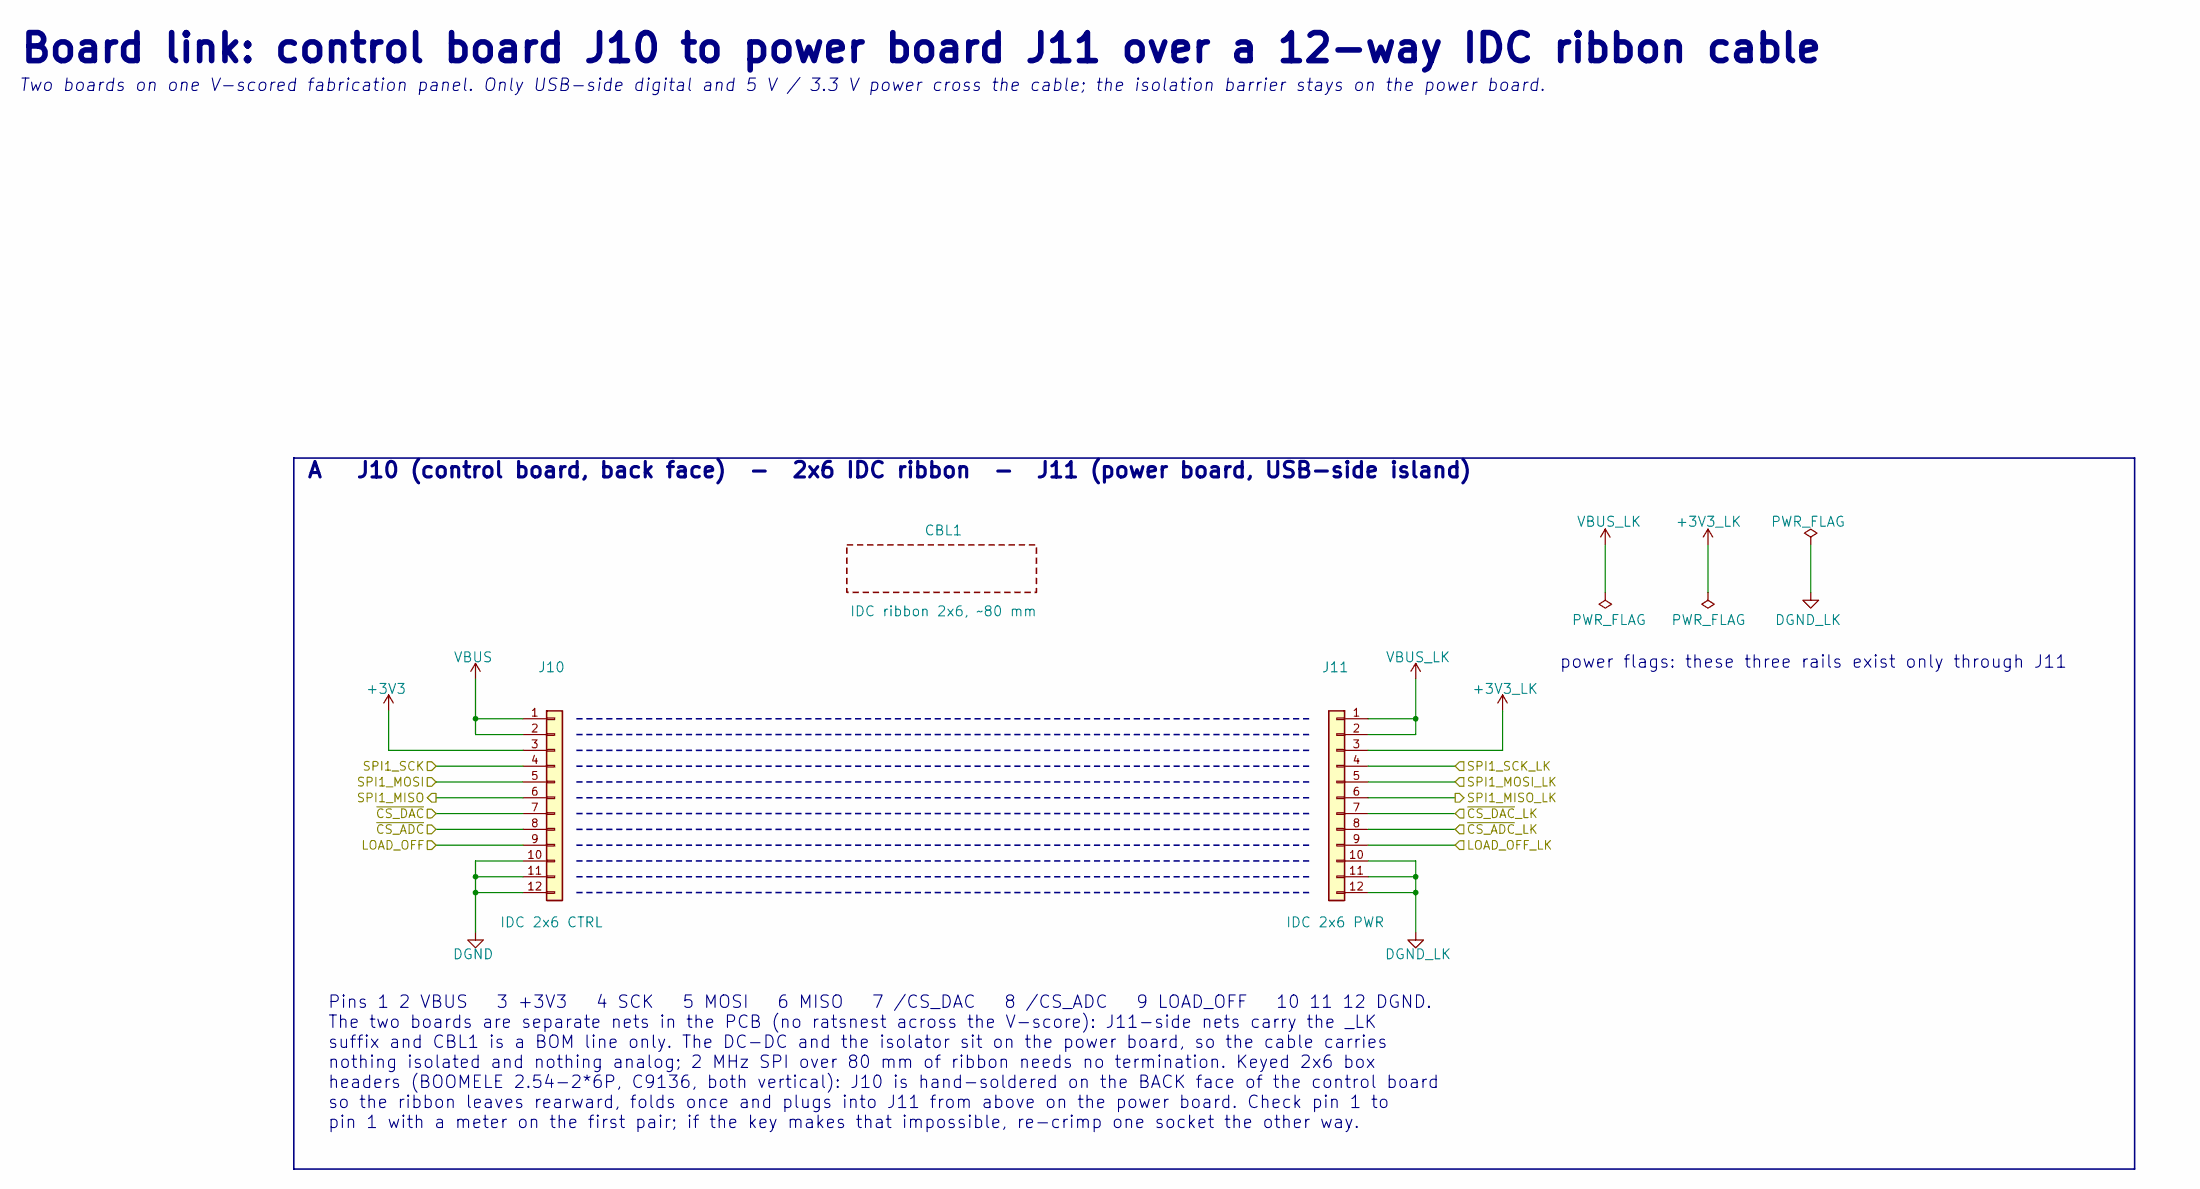
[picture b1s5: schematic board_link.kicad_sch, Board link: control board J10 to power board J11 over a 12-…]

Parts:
CBL1: IDC ribbon 2x6, ~80 mm; MPN 12-way 1.27 mm ribbon, about 80 mm, two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
J10: IDC 2x6 CTRL; IDC-Header_2x06_P2.54mm_Vertical; MPN 2x6 shrouded box header 2.54 mm, BOOMEL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; LCSC C9136
J11: IDC 2x6 PWR; IDC-Header_2x06_P2.54mm_Vertical; MPN 2x6 shrouded box header 2.54 mm, BOOMEL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; LCSC C9136

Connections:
+3V3: J10.3; also elsewhere on the board
+3V3_LK: J11.3; also elsewhere on the board
/Board Link/LOAD_OFF: J10.9; also elsewhere on the board
/Board Link/LOAD_OFF_LK: J11.9; also elsewhere on the board
/Board Link/SPI1_MISO: J10.6; also elsewhere on the board
/Board Link/SPI1_MISO_LK: J11.6; also elsewhere on the board
/Board Link/SPI1_MOSI: J10.5; also elsewhere on the board
/Board Link/SPI1_MOSI_LK: J11.5; also elsewhere on the board
/Board Link/SPI1_SCK: J10.4; also elsewhere on the board
/Board Link/SPI1_SCK_LK: J11.4; also elsewhere on the board
/Board Link/~CS_ADC: J10.8; also elsewhere on the board
/Board Link/~CS_ADC_LK: J11.8; also elsewhere on the board
/Board Link/~CS_DAC: J10.7; also elsewhere on the board
/Board Link/~CS_DAC_LK: J11.7; also elsewhere on the board
DGND: J10.10, J10.11, J10.12; also elsewhere on the board
DGND_LK: J11.10, J11.11, J11.12; also elsewhere on the board
VBUS: J10.1, J10.2; also elsewhere on the board
VBUS_LK: J11.1, J11.2; also elsewhere on the board

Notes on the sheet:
Board link: control board J10 to power board J11 over a 12-way IDC ribbon cable
Two boards on one V-scored fabrication panel. Only USB-side digital and 5 V / 3.3 V power cross the cable; the isolation barrier stays on the power board.
power flags: these three rails exist only through J11
Pins 1 2 VBUS 3 +3V3 4 SCK 5 MOSI 6 MISO 7 /CS_DAC 8 /CS_ADC 9 LOAD_OFF 10 11 12 DGND. The two boards are separate nets in the PCB (no ratsnest across the V-score): J11-side nets carry the _LK suffix and CBL1 is a BOM line only. The DC-DC and the isolator sit on the power board, so the cable carrie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
A J10 (control board, back face) - 2x6 IDC ribbon - J11 (power board, USB-side island)
